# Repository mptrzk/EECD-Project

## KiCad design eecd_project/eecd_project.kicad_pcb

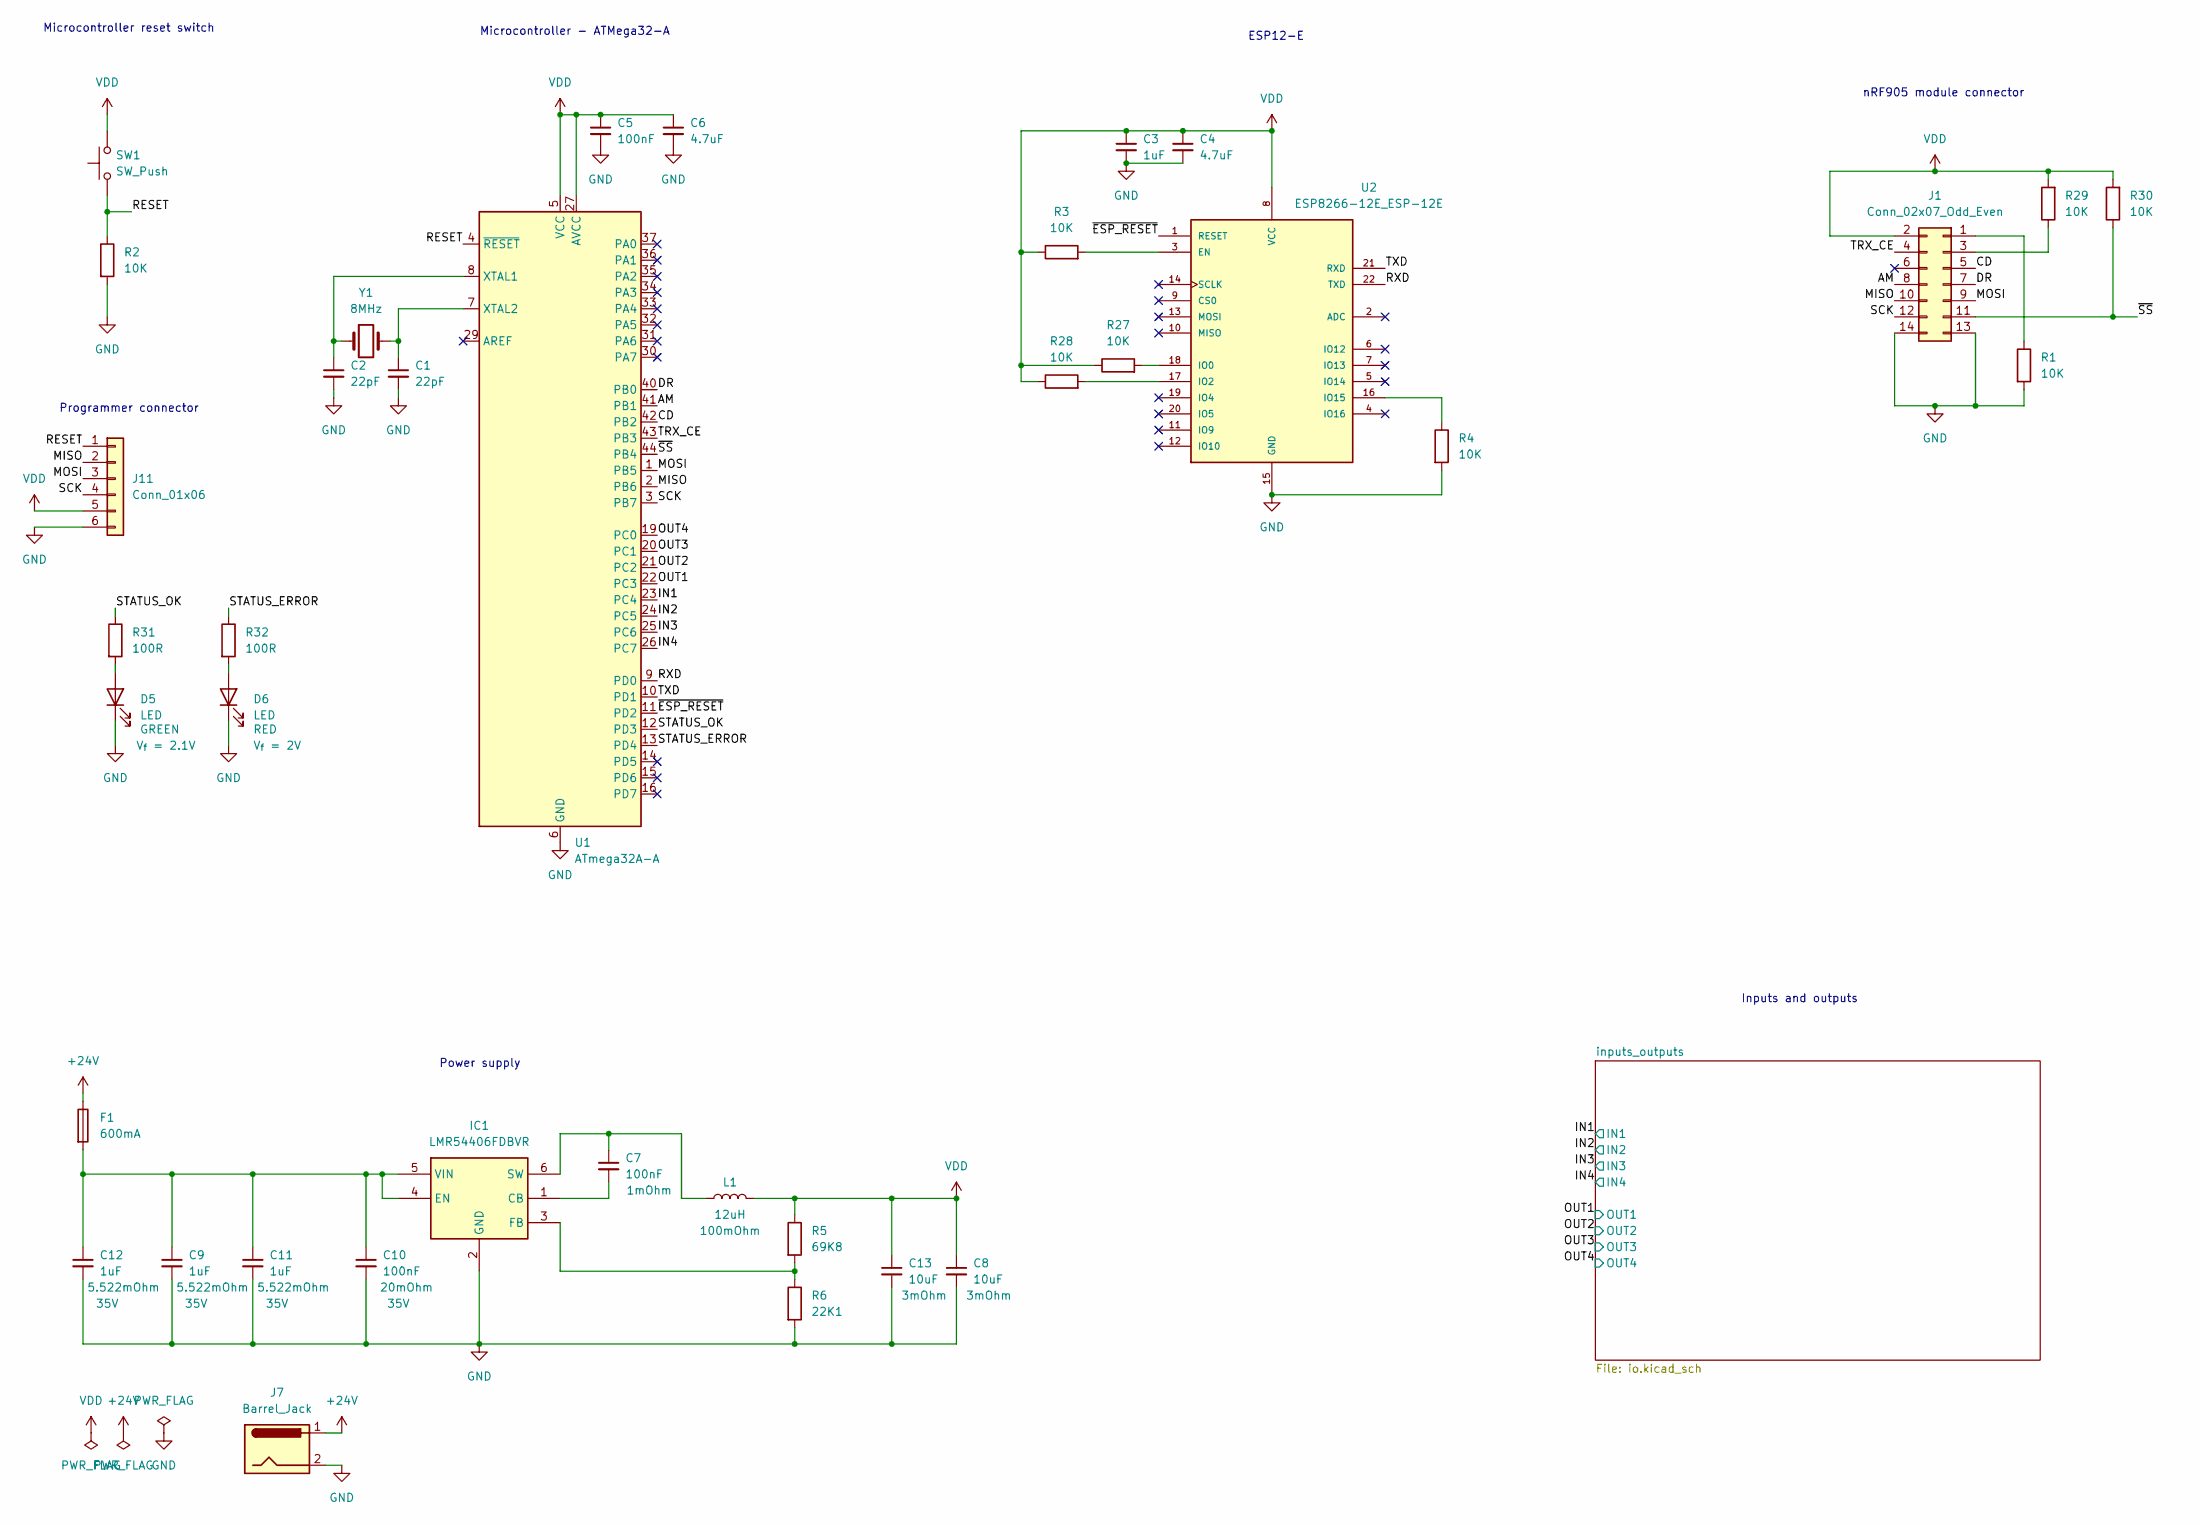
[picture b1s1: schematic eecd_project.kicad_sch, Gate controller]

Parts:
C1, C2: 22pF; C_0603_1608Metric_Pad1.08x0.95mm_HandSolder
C3, C9, C11, C12: 1uF; C_0603_1608Metric_Pad1.08x0.95mm_HandSolder
C4, C6: 4.7uF; C_0603_1608Metric_Pad1.08x0.95mm_HandSolder
C5, C7, C10: 100nF; C_0603_1608Metric_Pad1.08x0.95mm_HandSolder
C8, C13: 10uF; C_0603_1608Metric_Pad1.08x0.95mm_HandSolder
D5, D6: LED; LED_0603_1608Metric_Pad1.05x0.95mm_HandSolder
F1: 600mA; Fuseholder_Clip-5x20mm_Littelfuse_445-030_Inline_P20.50x5.2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
IC1: LMR54406FDBVR; SOT95P280X145-6N; Mouser Part Number 595-LMR54406FDBVR
J1: Conn_02x07_Odd_Even; PinSocket_2x07_P2.54mm_Vertical
J7: Barrel_Jack; BarrelJack_CUI_PJ-063AH_Horizontal
J11: Conn_01x06; Molex_PicoBlade_53047-0610_1x06_P1.25mm_Vertical
L1: 12uH; L_Bourns-SRN4018
R1, R2, R3, R4, R27, R28, R29, R30: 10K; R_0603_1608Metric_Pad0.98x0.95mm_HandSolder
R5: 69K8; R_0603_1608Metric_Pad0.98x0.95mm_HandSolder
R6: 22K1; R_0603_1608Metric_Pad0.98x0.95mm_HandSolder
R31, R32: 100R; R_0603_1608Metric_Pad0.98x0.95mm_HandSolder
SW1: SW_Push; SW_Tactile_SPST_Angled_PTS645Vx83-2LFS
U1: ATmega32A-A; TQFP-44_10x10mm_P0.8mm
U2: ESP8266-12E_ESP-12E; XCVR_ESP8266-12E_ESP-12E
Y1: 8MHz; XTAL_ABLS2_ABR

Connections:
+24V: F1.1, J7.1; also elsewhere on the board
/AM: J1.8, U1.41 (PB1)
/CD: J1.5, U1.42 (PB2)
/DR: J1.7, U1.40 (PB0)
/IN1: U1.23 (PC4); also elsewhere on the board
/IN2: U1.24 (PC5); also elsewhere on the board
/IN3: U1.25 (PC6); also elsewhere on the board
/IN4: U1.26 (PC7); also elsewhere on the board
/MISO: J1.10, J11.2, U1.2 (PB6)
/MOSI: J1.9, J11.3, U1.1 (PB5)
/OUT1: U1.22 (PC3); also elsewhere on the board
/OUT2: U1.21 (PC2); also elsewhere on the board
/OUT3: U1.20 (PC1); also elsewhere on the board
/OUT4: U1.19 (PC0); also elsewhere on the board
/RESET: J11.1, R2.1, SW1.1, U1.4 (~RESET)
/RXD: U1.9 (PD0), U2.22 (TXD)
/SCK: J1.12, J11.4, U1.3 (PB7)
/STATUS_ERROR: R32.1, U1.13 (PD4)
/STATUS_OK: R31.1, U1.12 (PD3)
/TRX_CE: J1.4, U1.43 (PB3)
/TXD: U1.10 (PD1), U2.21 (RXD)
/~ESP_RESET: U1.11 (PD2), U2.1 (RESET)
/~SS: J1.11, R30.1, U1.44 (PB4)
GND: C1.2, C2.2, C3.2, C4.2, C5.2, C6.2, C8.2, C9.2, C10.2, C11.2, C12.2, C13.2, D5.1 (K), D6.1 (K), IC1.2 (GND), J1.13, J1.14, J7.2, J11.6, R1.2, R2.2, R4.2, R6.2, U1.6 (GND), U1.18 (GND), U1.28 (GND), U1.39 (GND), U2.15 (GND); also elsewhere on the board
unnamed: D5.2 (A), R31.2
unnamed: D6.2 (A), R32.2
unnamed: C7.2, IC1.1 (CB)
unnamed: C9.1, C10.1, C11.1, C12.1, F1.2, IC1.4 (EN), IC1.5 (VIN)
unnamed: IC1.3 (FB), R5.2, R6.1
unnamed: C7.1, IC1.6 (SW), L1.1
unnamed: J1.1, R1.1
unnamed: J1.3, R29.1
unnamed: C2.1, U1.8 (XTAL1), Y1.1
unnamed: C1.1, U1.7 (XTAL2), Y1.2
unnamed: R3.2, U2.3 (EN)
unnamed: R27.2, U2.18 (IO0)
unnamed: R28.2, U2.17 (IO2)
unnamed: R4.1, U2.16 (IO15)
VDD: C3.1, C4.1, C5.1, C6.1, C8.1, C13.1, J1.2, J11.5, L1.2, R3.1, R5.1, R27.1, R28.1, R29.2, R30.2, SW1.2, U1.5 (VCC), U1.17 (VCC), U1.27 (AVCC), U1.38 (VCC), U2.8 (VCC); also elsewhere on the board

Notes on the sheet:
Power supply
nRF905 module connector
Inputs and outputs
Microcontroller reset switch
Microcontroller - ATMega32-A
ESP12-E
Programmer connector

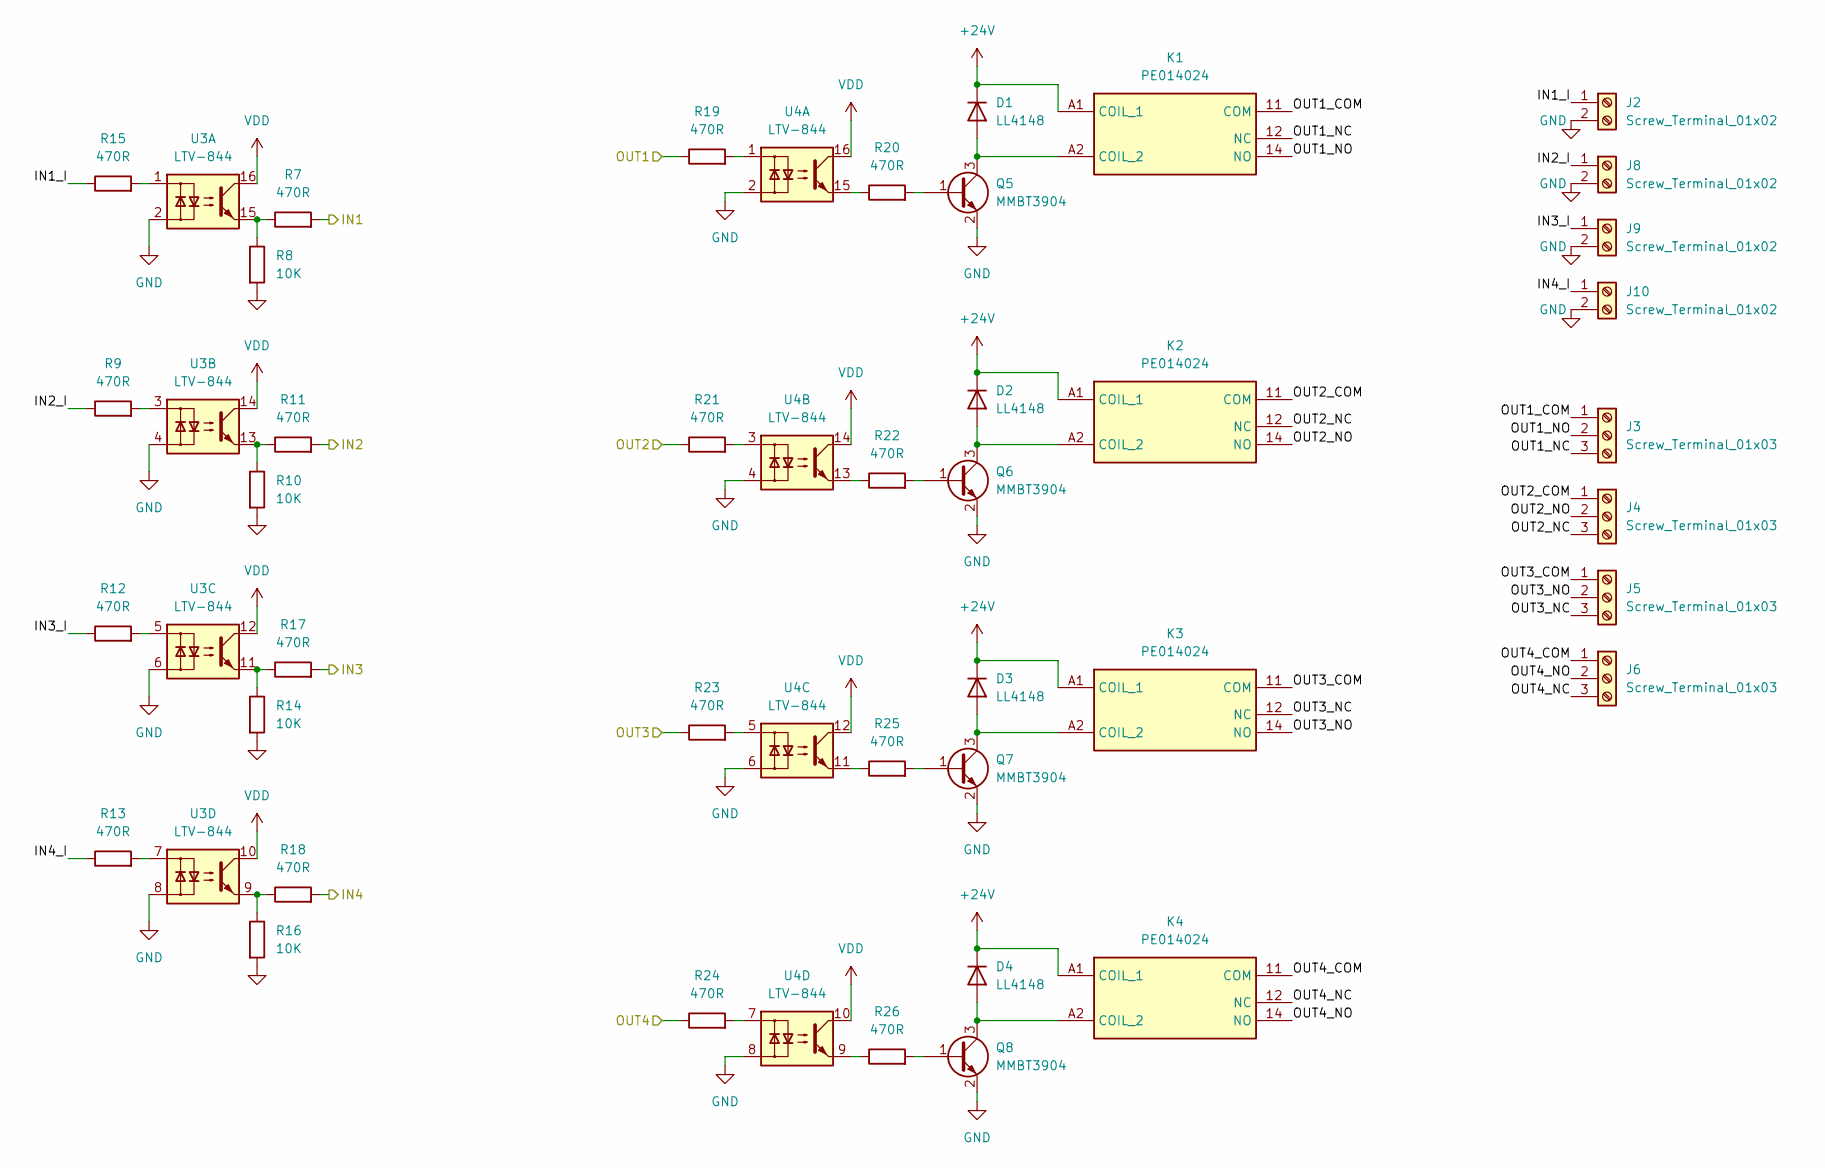
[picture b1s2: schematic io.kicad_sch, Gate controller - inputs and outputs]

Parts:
D1, D2, D3, D4: LL4148; D_MiniMELF
J2, J8, J9, J10: Screw_Terminal_01x02; CUI_TB001-500-P02BE
J3, J4, J5, J6: Screw_Terminal_01x03; CUI_TB010-508-03BE
K1, K2, K3, K4: PE014024; Mouser Part Number 655-PE014024
Q5, Q6, Q7, Q8: MMBT3904; SOT-23
R7, R9, R11, R12, R13, R15, R17, R18, R19, R20, R21, R22, R23, R24, R25, R26: 470R; R_0603_1608Metric_Pad0.98x0.95mm_HandSolder
R8, R10, R14, R16: 10K; R_0603_1608Metric_Pad0.98x0.95mm_HandSolder
U3, U4: LTV-844; DIP-16_W7.62mm

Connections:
+24V: D1.1 (K), D2.1 (K), D3.1 (K), D4.1 (K), K1.A1 (COIL_1), K2.A1 (COIL_1), K3.A1 (COIL_1), K4.A1 (COIL_1); also elsewhere on the board
/IN1: R7.2; also elsewhere on the board
/IN2: R11.2; also elsewhere on the board
/IN3: R17.2; also elsewhere on the board
/IN4: R18.2; also elsewhere on the board
/OUT1: R19.1; also elsewhere on the board
/OUT2: R21.1; also elsewhere on the board
/OUT3: R23.1; also elsewhere on the board
/OUT4: R24.1; also elsewhere on the board
/inputs_outputs/IN1_I: J2.1, R15.1
/inputs_outputs/IN2_I: J8.1, R9.1
/inputs_outputs/IN3_I: J9.1, R12.1
/inputs_outputs/IN4_I: J10.1, R13.1
/inputs_outputs/OUT1_COM: J3.1, K1.11 (COM)
/inputs_outputs/OUT1_NC: J3.3, K1.12 (NC)
/inputs_outputs/OUT1_NO: J3.2, K1.14 (NO)
/inputs_outputs/OUT2_COM: J4.1, K2.11 (COM)
/inputs_outputs/OUT2_NC: J4.3, K2.12 (NC)
/inputs_outputs/OUT2_NO: J4.2, K2.14 (NO)
/inputs_outputs/OUT3_COM: J5.1, K3.11 (COM)
/inputs_outputs/OUT3_NC: J5.3, K3.12 (NC)
/inputs_outputs/OUT3_NO: J5.2, K3.14 (NO)
/inputs_outputs/OUT4_COM: J6.1, K4.11 (COM)
/inputs_outputs/OUT4_NC: J6.3, K4.12 (NC)
/inputs_outputs/OUT4_NO: J6.2, K4.14 (NO)
GND: J2.2, J8.2, J9.2, J10.2, Q5.2 (E), Q6.2 (E), Q7.2 (E), Q8.2 (E), R8.2, R10.2, R14.2, R16.2, U3.2, U3.4, U3.6, U3.8, U4.2, U4.4, U4.6, U4.8; also elsewhere on the board
unnamed: D1.2 (A), K1.A2 (COIL_2), Q5.3 (C)
unnamed: D2.2 (A), K2.A2 (COIL_2), Q6.3 (C)
unnamed: D3.2 (A), K3.A2 (COIL_2), Q7.3 (C)
unnamed: D4.2 (A), K4.A2 (COIL_2), Q8.3 (C)
unnamed: Q5.1 (B), R20.2
unnamed: Q6.1 (B), R22.2
unnamed: Q7.1 (B), R25.2
unnamed: Q8.1 (B), R26.2
unnamed: R7.1, R8.1, U3.15
unnamed: R9.2, U3.3
unnamed: R10.1, R11.1, U3.13
unnamed: R12.2, U3.5
unnamed: R13.2, U3.7
unnamed: R14.1, R17.1, U3.11
unnamed: R15.2, U3.1
unnamed: R16.1, R18.1, U3.9
unnamed: R19.2, U4.1
unnamed: R20.1, U4.15
unnamed: R21.2, U4.3
unnamed: R22.1, U4.13
unnamed: R23.2, U4.5
unnamed: R24.2, U4.7
unnamed: R25.1, U4.11
unnamed: R26.1, U4.9
VDD: U3.10, U3.12, U3.14, U3.16, U4.10, U4.12, U4.14, U4.16; also elsewhere on the board

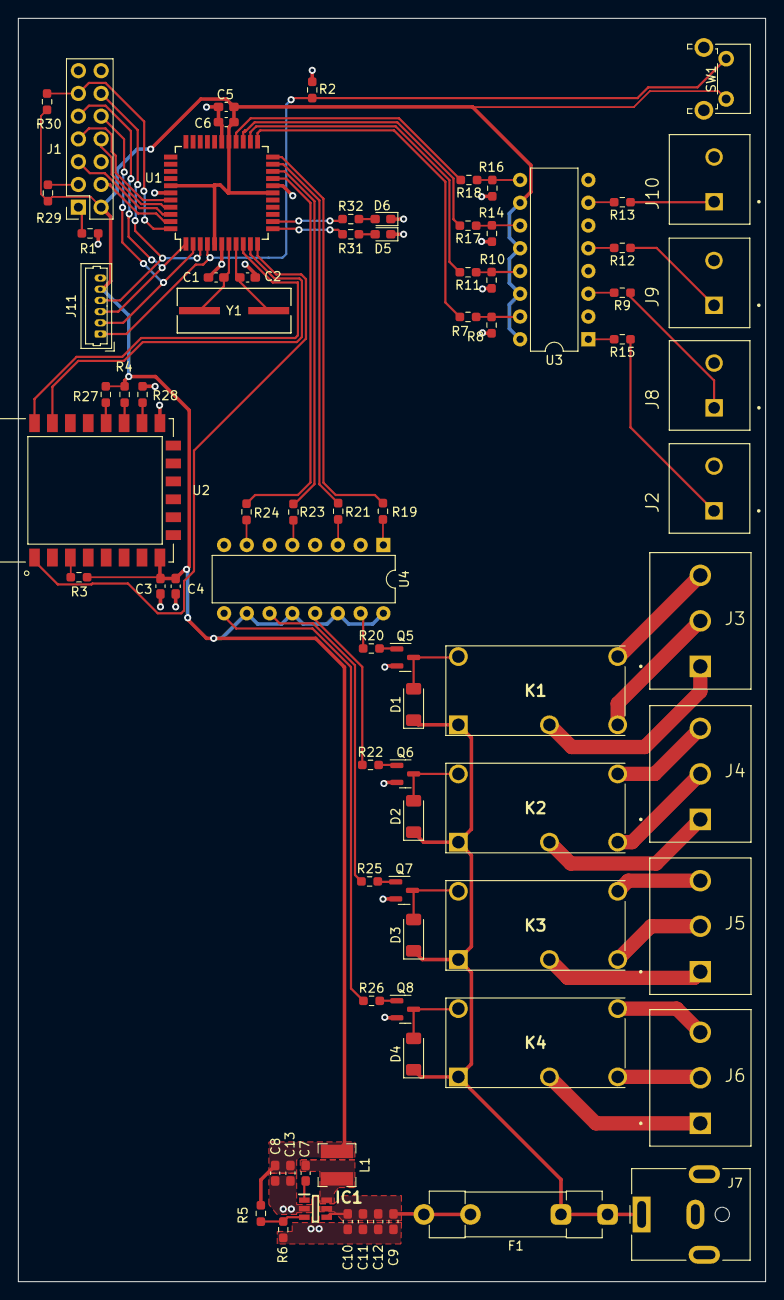
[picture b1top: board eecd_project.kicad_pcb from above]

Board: 2 copper layers, 83.4 x 141.0 mm, 79 parts (0 on the bottom side), 79 nets.

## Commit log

2023-12-04 before relays
2024-01-30 deleted "notes"
